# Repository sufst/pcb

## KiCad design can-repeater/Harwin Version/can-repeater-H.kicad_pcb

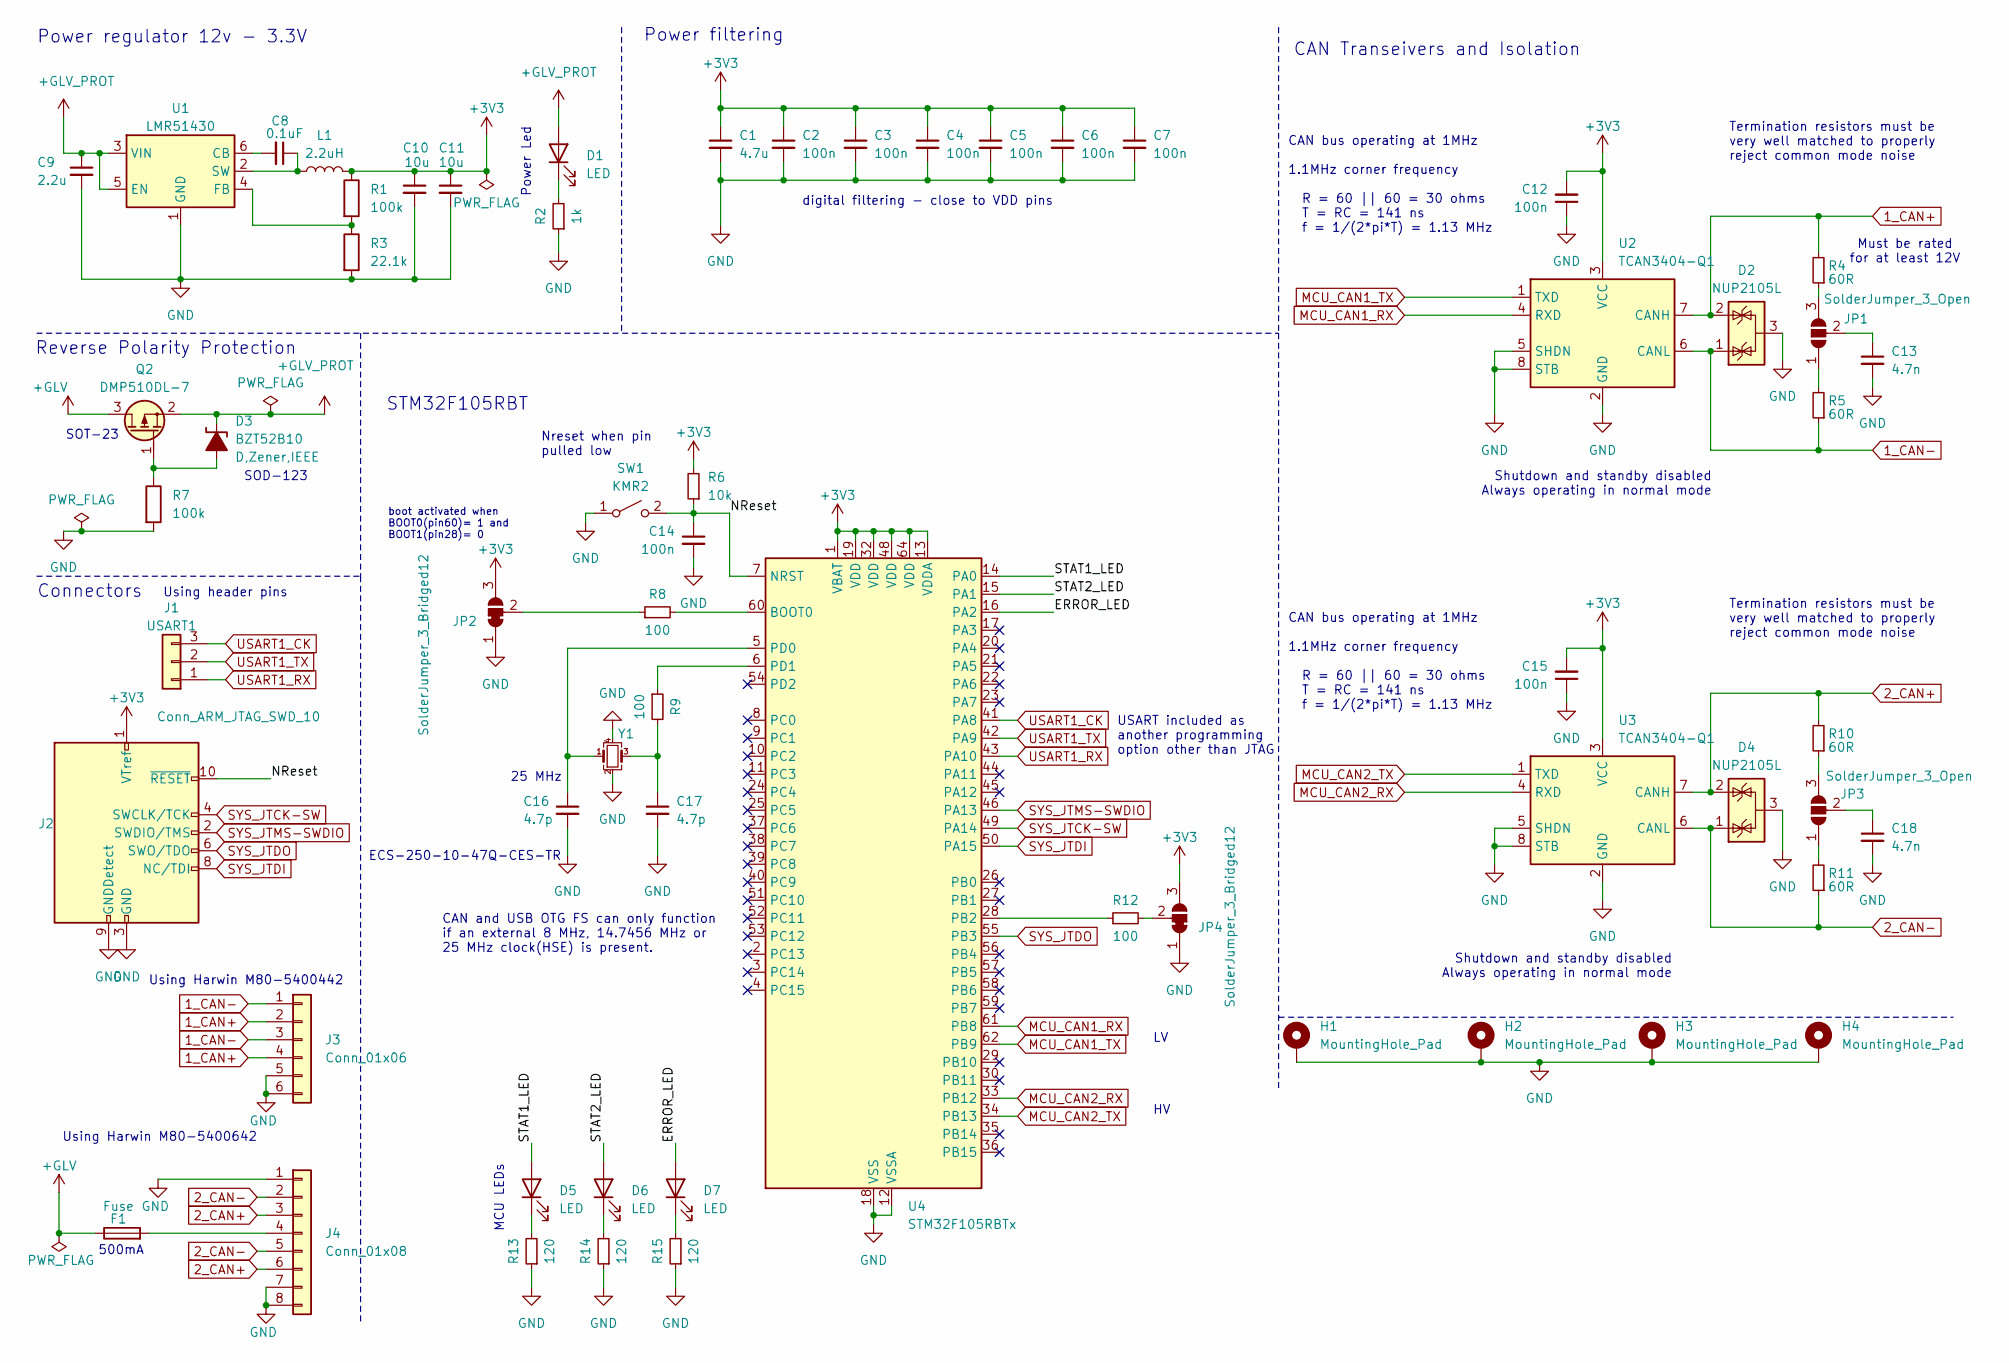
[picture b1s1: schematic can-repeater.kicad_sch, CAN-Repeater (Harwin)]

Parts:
C1: 4.7u; C_0805_2012Metric_Pad1.18x1.45mm_HandSolder
C2, C3, C4, C5, C6, C7, C12, C14, C15: 100n; C_0603_1608Metric_Pad1.08x0.95mm_HandSolder
C8: 0.1uF; C_0603_1608Metric_Pad1.08x0.95mm_HandSolder
C9: 2.2u; C_0603_1608Metric_Pad1.08x0.95mm_HandSolder
C10, C11: 10u; C_0805_2012Metric_Pad1.18x1.45mm_HandSolder
C13, C18: 4.7n; C_0603_1608Metric_Pad1.08x0.95mm_HandSolder
C16, C17: 4.7p; C_0603_1608Metric_Pad1.08x0.95mm_HandSolder
D1, D5, D6, D7: LED; LED_0805_2012Metric_Pad1.15x1.40mm_HandSolder
D2, D4: NUP2105L; SOT-23; MPN NUP2105L
D3: BZT52B10; D_SOD-123; MPN BZT52B10
F1: Fuse; Fuse_0603_1608Metric_Pad1.05x0.95mm_HandSolder
H1, H2, H3, H4: MountingHole_Pad; MountingHole_2.2mm_M2_DIN965_Pad_TopBottom
J1: USART1; PinHeader_1x03_P2.54mm_Vertical
J2: Conn_ARM_JTAG_SWD_10; SHF10501LDSMLC; MPN SHF-105-01-L-D-SM-LC
J3: Conn_01x06; M80-5400442; MPN M80-5400442
J4: Conn_01x08; M80-5400642; MPN M80-5400642
JP1, JP3: SolderJumper_3_Open; SolderJumper-3_P1.3mm_Open_RoundedPad1.0x1.5mm
JP2, JP4: SolderJumper_3_Bridged12; SolderJumper-3_P1.3mm_Bridged12_RoundedPad1.0x1.5mm
L1: 2.2uH; L_Coilcraft_XAL4020-XXX; MPN XAL4020-222MEC
Q2: DMP510DL-7; SOT-23
R1, R7: 100k; R_0603_1608Metric_Pad0.98x0.95mm_HandSolder
R2: 1k; R_0603_1608Metric_Pad0.98x0.95mm_HandSolder
R3: 22.1k; R_0603_1608Metric_Pad0.98x0.95mm_HandSolder
R4, R5, R10, R11: 60R; R_0603_1608Metric_Pad0.98x0.95mm_HandSolder
R6: 10k; R_0603_1608Metric_Pad0.98x0.95mm_HandSolder
R8, R9, R12: 100; R_0603_1608Metric_Pad0.98x0.95mm_HandSolder
R13, R14, R15: 120; R_0603_1608Metric_Pad0.98x0.95mm_HandSolder
SW1: KMR2; SW_Push_1P1T_NO_CK_KMR2; MPN KMR221NG LFS
U1: LMR51430; SOT-23-6; MPN LMR51430YDDCR
U2, U3: TCAN3404-Q1; SOT-23-8_Handsoldering; MPN TCAN3404DDFRQ1
U4: STM32F105RBTx; LQFP-64_10x10mm_P0.5mm; MPN STM32F105RBT6
Y1: ECS-250-10-47Q-CES-TR; Resonator_SMD_ECS_ECX-1247Q_1.6x1.2x0.3mm; MPN ECS-250-10-47Q-CES-TR

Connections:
1_CAN+: D2.2 (K), J3.2, J3.4, R4.2, U2.7 (CANH)
1_CAN-: D2.1 (K), J3.1, J3.3, R5.1, U2.6 (CANL)
2_CAN+: D4.2 (K), J4.3, J4.6, R10.2, U3.7 (CANH)
2_CAN-: D4.1 (K), J4.2, J4.5, R11.1, U3.6 (CANL)
+3V3: C1.1, C2.1, C3.1, C4.1, C5.1, C6.1, C7.1, C10.1, C11.1, C12.2, C15.2, J2.1 (VTref), JP2.3 (B), JP4.3 (B), L1.2, R1.1, R6.2, U2.3 (VCC), U3.3 (VCC), U4.1 (VBAT), U4.13 (VDDA), U4.19 (VDD), U4.32 (VDD), U4.48 (VDD), U4.64 (VDD)
+GLV: F1.1, Q2.3 (D)
+GLV_PROT: C9.1, D1.2 (A), D3.1 (K-), Q2.2 (S), U1.3 (VIN), U1.5 (EN)
/ERROR_LED: D7.2 (A), U4.16 (PA2)
/NReset: C14.1, J2.10 (~RESET), R6.1, SW1.2 (B), U4.7 (NRST)
/STAT1_LED: D5.2 (A), U4.14 (PA0)
/STAT2_LED: D6.2 (A), U4.15 (PA1)
GND: C1.2, C2.2, C3.2, C4.2, C5.2, C6.2, C7.2, C9.2, C10.2, C11.2, C12.1, C13.2, C14.2, C15.1, C16.2, C17.2, C18.2, D2.3 (A), D4.3 (A), H1.1, H2.1, H3.1, H4.1, J2.3 (GND), J2.5 (GND), J2.9 (GNDDetect), J3.5, J3.6, J4.1, J4.7, J4.8, JP2.1 (A), JP4.1 (A), R2.1, R3.2, R7.2, R13.1, R14.1, R15.1, SW1.1 (A), U1.1 (GND), U2.2 (GND), U2.5 (SHDN), U2.8 (STB), U3.2 (GND), U3.5 (SHDN), U3.8 (STB), U4.12 (VSSA), U4.18 (VSS), U4.31 (VSS), U4.47 (VSS), U4.63 (VSS), Y1.2, Y1.4
MCU_CAN1_RX: U2.4 (RXD), U4.61 (PB8)
MCU_CAN1_TX: U2.1 (TXD), U4.62 (PB9)
MCU_CAN2_RX: U3.4 (RXD), U4.33 (PB12)
MCU_CAN2_TX: U3.1 (TXD), U4.34 (PB13)
unnamed: C17.1, R9.2, Y1.3
unnamed: D1.1 (K), R2.2
unnamed: D3.2 (A+), Q2.1 (G), R7.1
unnamed: D5.1 (K), R13.2
unnamed: D6.1 (K), R14.2
unnamed: D7.1 (K), R15.2
unnamed: F1.2, J4.4
unnamed: JP1.1 (A), R5.2
unnamed: JP1.3 (B), R4.1
unnamed: C13.1, JP1.2 (C)
unnamed: JP2.2 (C), R8.1
unnamed: JP3.1 (A), R11.2
unnamed: JP3.3 (B), R10.1
unnamed: C18.1, JP3.2 (C)
unnamed: JP4.2 (C), R12.2
unnamed: C8.2, U1.6 (CB)
unnamed: R1.2, R3.1, U1.4 (FB)
unnamed: C8.1, L1.1, U1.2 (SW)
unnamed: R8.2, U4.60 (BOOT0)
unnamed: R12.1, U4.28 (PB2)
unnamed: C16.1, U4.5 (PD0), Y1.1
unnamed: R9.1, U4.6 (PD1)
SYS_JTCK-SW: J2.4 (SWCLK/TCK), U4.49 (PA14)
SYS_JTDI: J2.8 (NC/TDI), U4.50 (PA15)
SYS_JTDO: J2.6 (SWO/TDO), U4.55 (PB3)
SYS_JTMS-SWDIO: J2.2 (SWDIO/TMS), U4.46 (PA13)
USART1_CK: J1.3, U4.41 (PA8)
USART1_RX: J1.1, U4.43 (PA10)
USART1_TX: J1.2, U4.42 (PA9)

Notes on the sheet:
Using header pins
Shutdown and standby disabled Always operating in normal mode
MCU LEDs
SOT-23
ECS-250-10-47Q-CES-TR
Termination resistors must be very well matched to properly reject common mode noise
boot activated when BOOT0(pin60)= 1 and BOOT1(pin28)= 0
CAN and USB OTG FS can only function if an external 8 MHz, 14.7456 MHz or 25 MHz clock(HSE) is present.
Using Harwin M80-5400442
Power Led
Power regulator 12v - 3.3V
Nreset when pin pulled low
Reverse Polarity Protection
digital filtering - close to VDD pins
CAN bus operating at 1MHz 1.1MHz corner frequency R = 60 || 60 = 30 ohms T = RC = 141 ns f = 1/(2*pi*T) = 1.13 MHz
SOD-123
CAN Transeivers and Isolation
500mA
Connectors
STM32F105RBT
25 MHz
Using Harwin M80-5400642
Must be rated for at least 12V
USART included as another programming option other than JTAG
Power filtering

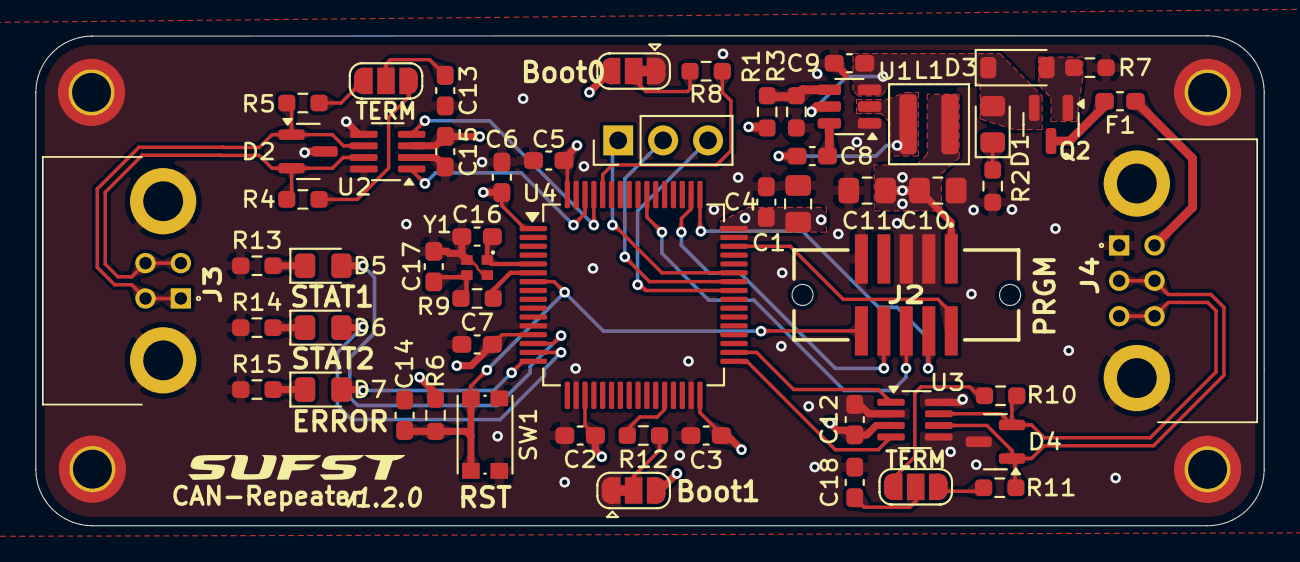
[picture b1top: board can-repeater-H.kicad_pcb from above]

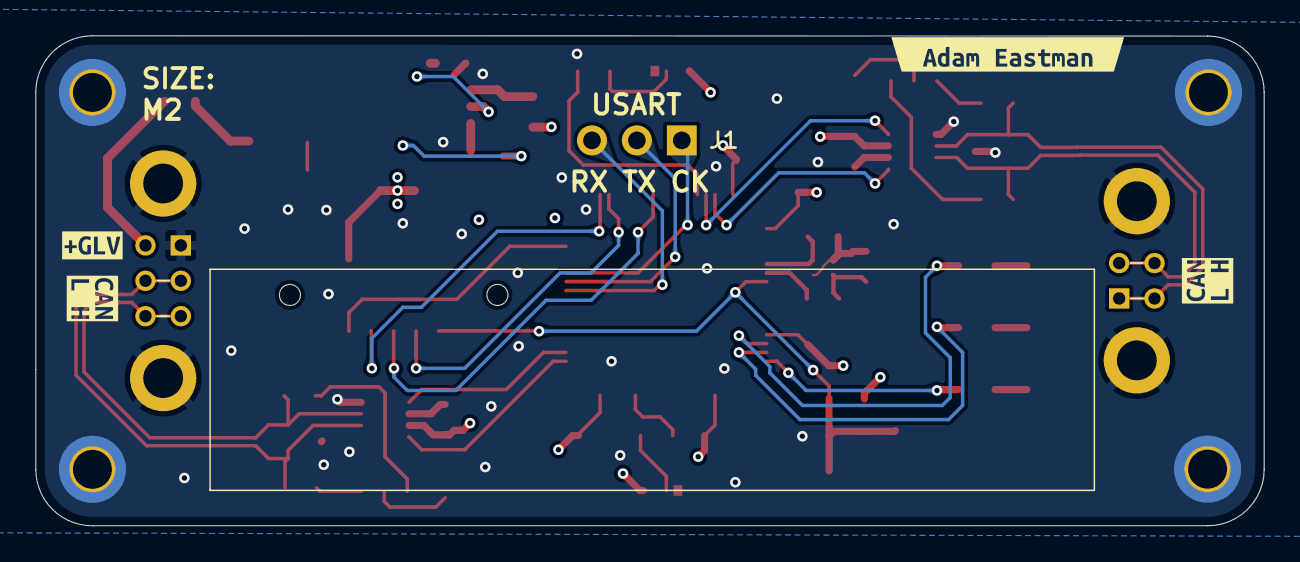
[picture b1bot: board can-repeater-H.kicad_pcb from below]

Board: 4 copper layers, 69.5 x 27.7 mm, 65 parts (4 on the bottom side), 45 nets.

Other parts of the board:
kibuzzard-694AF8B0: G***; kibuzzard-694AF8B0
kibuzzard-694AF877: G***; kibuzzard-694AF877
kibuzzard-6972BB08: G***; kibuzzard-6972BB08
kibuzzard-6972C6E9: G***; kibuzzard-6972C6E9

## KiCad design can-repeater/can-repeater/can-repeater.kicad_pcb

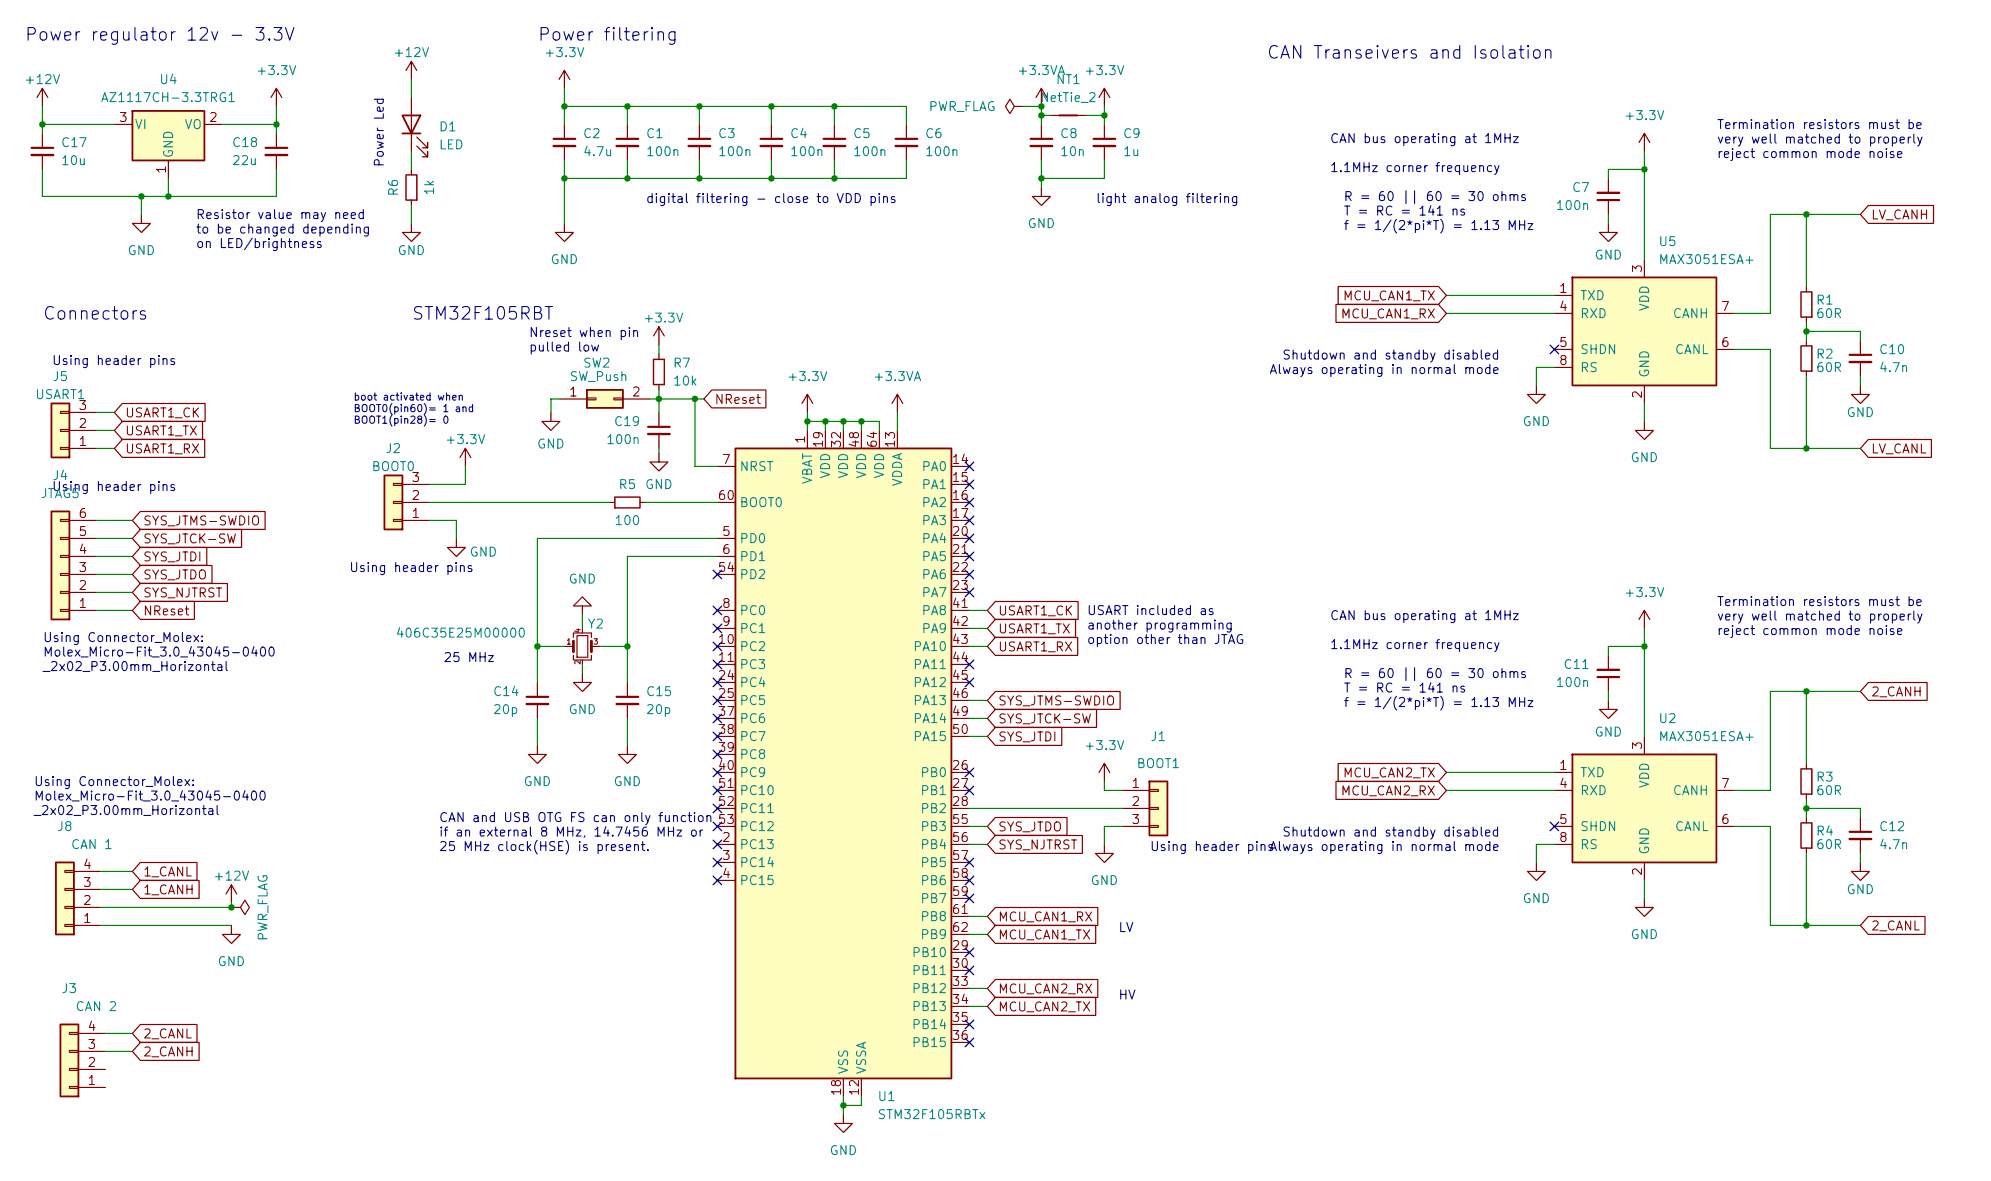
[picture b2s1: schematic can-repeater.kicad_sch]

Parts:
C1, C3, C4, C5, C6, C7, C11, C19: 100n; C_0805_2012Metric_Pad1.18x1.45mm_HandSolder
C2: 4.7u; C_1206_3216Metric_Pad1.33x1.80mm_HandSolder
C8: 10n; C_0805_2012Metric_Pad1.18x1.45mm_HandSolder
C9: 1u; C_0805_2012Metric_Pad1.18x1.45mm_HandSolder
C10, C12: 4.7n; C_0805_2012Metric_Pad1.18x1.45mm_HandSolder
C14, C15: 20p; C_0805_2012Metric_Pad1.18x1.45mm_HandSolder
C17: 10u; C_1206_3216Metric_Pad1.33x1.80mm_HandSolder
C18: 22u; C_1206_3216Metric_Pad1.33x1.80mm_HandSolder
D1: LED; LED_0805_2012Metric_Pad1.15x1.40mm_HandSolder
J1: BOOT1; PinHeader_1x03_P2.54mm_Vertical
J2: BOOT0; PinHeader_1x03_P2.54mm_Vertical
J3: CAN 2; Molex_Micro-Fit_3.0_43045-0400_2x02_P3.00mm_Horizontal
J4: JTAG5; PinHeader_1x06_P2.54mm_Vertical
J5: USART1; PinHeader_1x03_P2.54mm_Vertical
J8: CAN 1; Molex_Micro-Fit_3.0_43045-0400_2x02_P3.00mm_Horizontal
NT1: NetTie_2; NetTie-2_SMD_Pad0.5mm
R1, R2, R3, R4: 60R; R_0805_2012Metric_Pad1.20x1.40mm_HandSolder
R5: 100; R_0805_2012Metric_Pad1.20x1.40mm_HandSolder
R6: 1k; R_0805_2012Metric_Pad1.20x1.40mm_HandSolder
R7: 10k; R_0805_2012Metric_Pad1.20x1.40mm_HandSolder
SW2: SW_Push; PinHeader_1x02_P2.54mm_Vertical
U1: STM32F105RBTx; LQFP-64_10x10mm_P0.5mm
U2, U5: MAX3051ESA+; SOIC-8_3.9x4.9mm_P1.27mm
U4: AZ1117CH-3.3TRG1; SOT-223-3_TabPin2
Y2: 406C35E25M00000; Crystal_SMD_0603-4Pin_6.0x3.5mm_HandSoldering

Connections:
1_CANH: J8.3
1_CANL: J8.4
2_CANH: J3.3, R3.2, U2.7 (CANH)
2_CANL: J3.4, R4.1, U2.6 (CANL)
+3.3V: C1.1, C2.1, C3.1, C4.1, C5.1, C6.1, C7.2, C9.1, C11.2, C18.1, J1.1, J2.3, NT1.2, R7.2, U1.1 (VBAT), U1.19 (VDD), U1.32 (VDD), U1.48 (VDD), U1.64 (VDD), U2.3 (VDD), U4.2 (VO), U5.3 (VDD)
+3.3VA: C8.1, NT1.1, U1.13 (VDDA)
+12V: C17.1, D1.2 (A), J8.2, U4.3 (VI)
GND: C1.2, C2.2, C3.2, C4.2, C5.2, C6.2, C7.1, C8.2, C9.2, C10.2, C11.1, C12.2, C14.2, C15.2, C17.2, C18.2, C19.2, J1.3, J2.1, J8.1, R6.1, SW2.1, U1.12 (VSSA), U1.18 (VSS), U1.31 (VSS), U1.47 (VSS), U1.63 (VSS), U2.2 (GND), U2.8 (RS), U4.1 (GND), U5.2 (GND), U5.8 (RS), Y2.2, Y2.4
LV_CANH: R1.2, U5.7 (CANH)
LV_CANL: R2.1, U5.6 (CANL)
MCU_CAN1_RX: U1.61 (PB8), U5.4 (RXD)
MCU_CAN1_TX: U1.62 (PB9), U5.1 (TXD)
MCU_CAN2_RX: U1.33 (PB12), U2.4 (RXD)
MCU_CAN2_TX: U1.34 (PB13), U2.1 (TXD)
NReset: C19.1, J4.1, R7.1, SW2.2, U1.7 (NRST)
unnamed: C10.1, R1.1, R2.2
unnamed: C12.1, R3.1, R4.2
unnamed: D1.1 (K), R6.2
unnamed: J1.2, U1.28 (PB2)
unnamed: J2.2, R5.1
unnamed: R5.2, U1.60 (BOOT0)
unnamed: C14.1, U1.5 (PD0), Y2.1
unnamed: C15.1, U1.6 (PD1), Y2.3
SYS_JTCK-SW: J4.5, U1.49 (PA14)
SYS_JTDI: J4.4, U1.50 (PA15)
SYS_JTDO: J4.3, U1.55 (PB3)
SYS_JTMS-SWDIO: J4.6, U1.46 (PA13)
SYS_NJTRST: J4.2, U1.56 (PB4)
USART1_CK: J5.3, U1.41 (PA8)
USART1_RX: J5.1, U1.43 (PA10)
USART1_TX: J5.2, U1.42 (PA9)

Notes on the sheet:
Using header pins
Shutdown and standby disabled Always operating in normal mode
Termination resistors must be very well matched to properly reject common mode noise
boot activated when BOOT0(pin60)= 1 and BOOT1(pin28)= 0
CAN and USB OTG FS can only function if an external 8 MHz, 14.7456 MHz or 25 MHz clock(HSE) is present.
Using Connector_Molex: Molex_Micro-Fit_3.0_43045-0400 _2x02_P3.00mm_Horizontal
Power Led
Power regulator 12v - 3.3V
Nreset when pin pulled low
digital filtering - close to VDD pins
CAN bus operating at 1MHz 1.1MHz corner frequency R = 60 || 60 = 30 ohms T = RC = 141 ns f = 1/(2*pi*T) = 1.13 MHz
CAN Transeivers and Isolation
Resistor value may need to be changed depending on LED/brightness
light analog filtering
Connectors
STM32F105RBT
25 MHz
USART included as another programming option other than JTAG
Power filtering

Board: 2 copper layers, 37 parts (0 on the bottom side), 29 nets, no tracks yet.

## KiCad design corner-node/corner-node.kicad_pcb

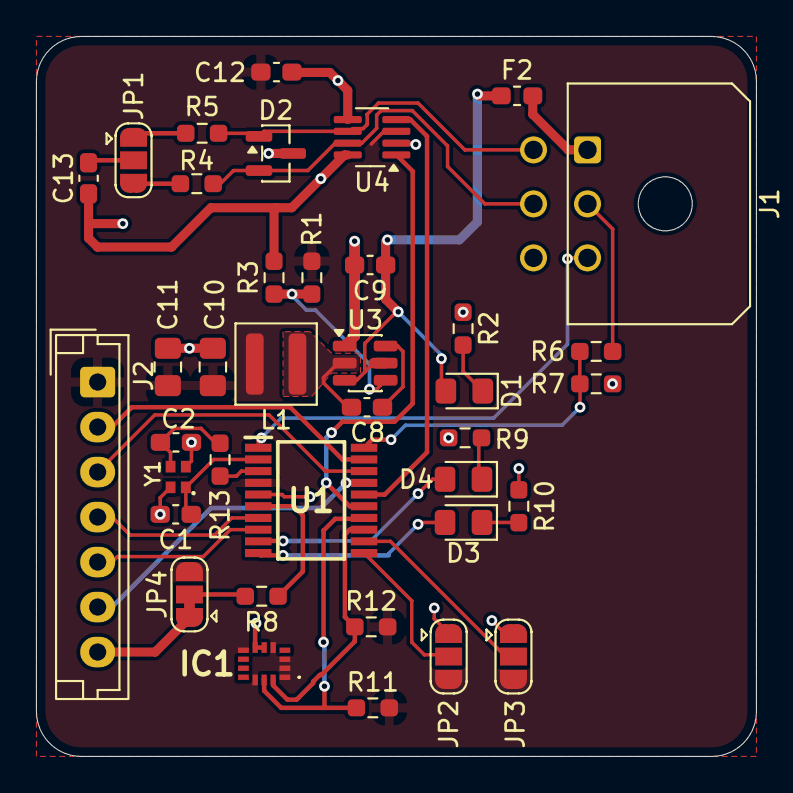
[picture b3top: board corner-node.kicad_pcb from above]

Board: 2 copper layers, 40.0 x 40.0 mm, 38 parts (0 on the bottom side), 36 nets.

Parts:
C1, C2: C; C_0603_1608Metric_Pad1.08x0.95mm_HandSolder
C8: 0.1uF; C_0603_1608Metric_Pad1.08x0.95mm_HandSolder
C9: 2.2u; C_0603_1608Metric_Pad1.08x0.95mm_HandSolder
C10, C11: 10u; C_0805_2012Metric_Pad1.18x1.45mm_HandSolder
C12: 100n; C_0603_1608Metric_Pad1.08x0.95mm_HandSolder
C13: 4.7n; C_0603_1608Metric_Pad1.08x0.95mm_HandSolder
D1, D3, D4: LED; LED_0805_2012Metric_Pad1.15x1.40mm_HandSolder
D2: NUP2105L; SOT-23
F2: Fuse; Fuse_0603_1608Metric_Pad1.05x0.95mm_HandSolder
IC1: LSM6DSV80XTR; LSM6DSV16BXTR
J1: Conn_01x06; Molex_Micro-Fit_3.0_43045-0600_2x03_P3.00mm_Horizontal
J2: Conn_01x07; JST_EH_B7B-EH-A_1x07_P2.50mm_Vertical
JP1, JP2, JP3: SolderJumper_3_Open; SolderJumper-3_P1.3mm_Open_RoundedPad1.0x1.5mm
JP4: SolderJumper_3_Bridged12; SolderJumper-3_P1.3mm_Bridged12_RoundedPad1.0x1.5mm
L1: 2.2uH; L_Coilcraft_XAL4020-XXX
R1: 100k; R_0603_1608Metric_Pad0.98x0.95mm_HandSolder
R2: 1k; R_0603_1608Metric_Pad0.98x0.95mm_HandSolder
R3: 22.1k; R_0603_1608Metric_Pad0.98x0.95mm_HandSolder
R4, R5: 60R; R_0603_1608Metric_Pad0.98x0.95mm_HandSolder
R6: 30k; R_0603_1608Metric_Pad0.98x0.95mm_HandSolder
R7: 10k; R_0603_1608Metric_Pad0.98x0.95mm_HandSolder
R8, R13: 100; R_0603_1608Metric_Pad0.98x0.95mm_HandSolder
R9, R10: 120; R_0603_1608Metric_Pad0.98x0.95mm_HandSolder
R11, R12: 4.7k; R_0603_1608Metric_Pad0.98x0.95mm_HandSolder
U1: SOP65P640X120-20N
U3: LMR51430; SOT-23-6
U4: TCAN3404-Q1; SOT-23-8_Handsoldering
Y1: ECS-250-10-47Q-CES-TR; Resonator_SMD_ECS_ECX-1247Q_1.6x1.2x0.3mm

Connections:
1_CAN+: D2.2 (K), J1.5, R4.2, U4.7 (CANH)
1_CAN-: D2.1 (K), J1.4, R5.1, U4.6 (CANL)
+3V3: C10.1, C11.1, C12.2, IC1.1 (SDO/SA0), IC1.2 (SDX), IC1.3 (SCX), IC1.5 (VDDIO), IC1.8 (VDD), IC1.12 (CS), J2.1, JP2.3 (B), JP3.3 (B), JP4.3 (B), L1.2, R1.1, R11.2, R12.2, U1.4 (VDD), U4.3 (VCC)
+GLV_PROT: C9.1, D1.2 (A), F2.1, U3.3 (VIN), U3.5 (EN)
/BOOT0: R8.1, U1.6 (PF2)
/DEBUG_SWCLK: J2.2, U1.19 (PA14)
/DEBUG_SWDIO: J2.3, U1.18 (PA13)
/ERROR_LED: D3.2 (A), U1.10 (PA3)
/FDCAN1_RX: U1.16 (PA11), U4.4 (RXD)
/FDCAN1_TX: U1.15 (PB0), U4.1 (TXD)
/I2C2_SCL: IC1.13 (SCL), R11.1, U1.14 (PA7)
/I2C2_SDA: IC1.14 (SDA), R12.1, U1.13 (PA6)
/PPS_IN: J1.3, U1.1 (PB7)
/RCC_OSCX_IN: C1.1, U1.2 (PC14), Y1.1
/RCC_OSCX_OUT: R13.1, U1.3 (PC15)
/STATUS1_LED: D4.2 (A), U1.9 (PA2)
/USART1_CK: J2.6, U1.17 (PA12)
/USART1_RX: J2.5, U1.8 (PA1)
/USART1_TX: J2.4, U1.7 (PA0)
/WHEELSPEED IN: R6.2, R7.1, U1.20 (PB3)
/WHEELSPEED sensor: J1.2, R6.1
/WHEEL_ID0: JP2.2 (C), U1.11 (PA4)
/WHEEL_ID1: JP3.2 (C), U1.12 (PA5)
GND: C1.2, C2.2, C9.2, C10.2, C11.2, C12.1, C13.2, D2.3 (A), IC1.6 (GND_1), IC1.7 (GND_2), J1.6, J2.7, JP2.1 (A), JP3.1 (A), JP4.1 (A), R2.1, R3.2, R7.2, R9.1, R10.1, U1.5 (VSS), U3.1 (GND), U4.2 (GND), U4.5 (SHDN), U4.8 (STB), Y1.2, Y1.4
unnamed: C2.1, R13.2, Y1.3
unnamed: D1.1 (K), R2.2
unnamed: D3.1 (K), R10.2
unnamed: D4.1 (K), R9.2
unnamed: F2.2, J1.1
unnamed: JP1.1 (A), R5.2
unnamed: JP1.3 (B), R4.1
unnamed: C13.1, JP1.2 (C)
unnamed: JP4.2 (C), R8.2
unnamed: C8.2, U3.6 (CB)
unnamed: R1.2, R3.1, U3.4 (FB)
unnamed: C8.1, L1.1, U3.2 (SW)

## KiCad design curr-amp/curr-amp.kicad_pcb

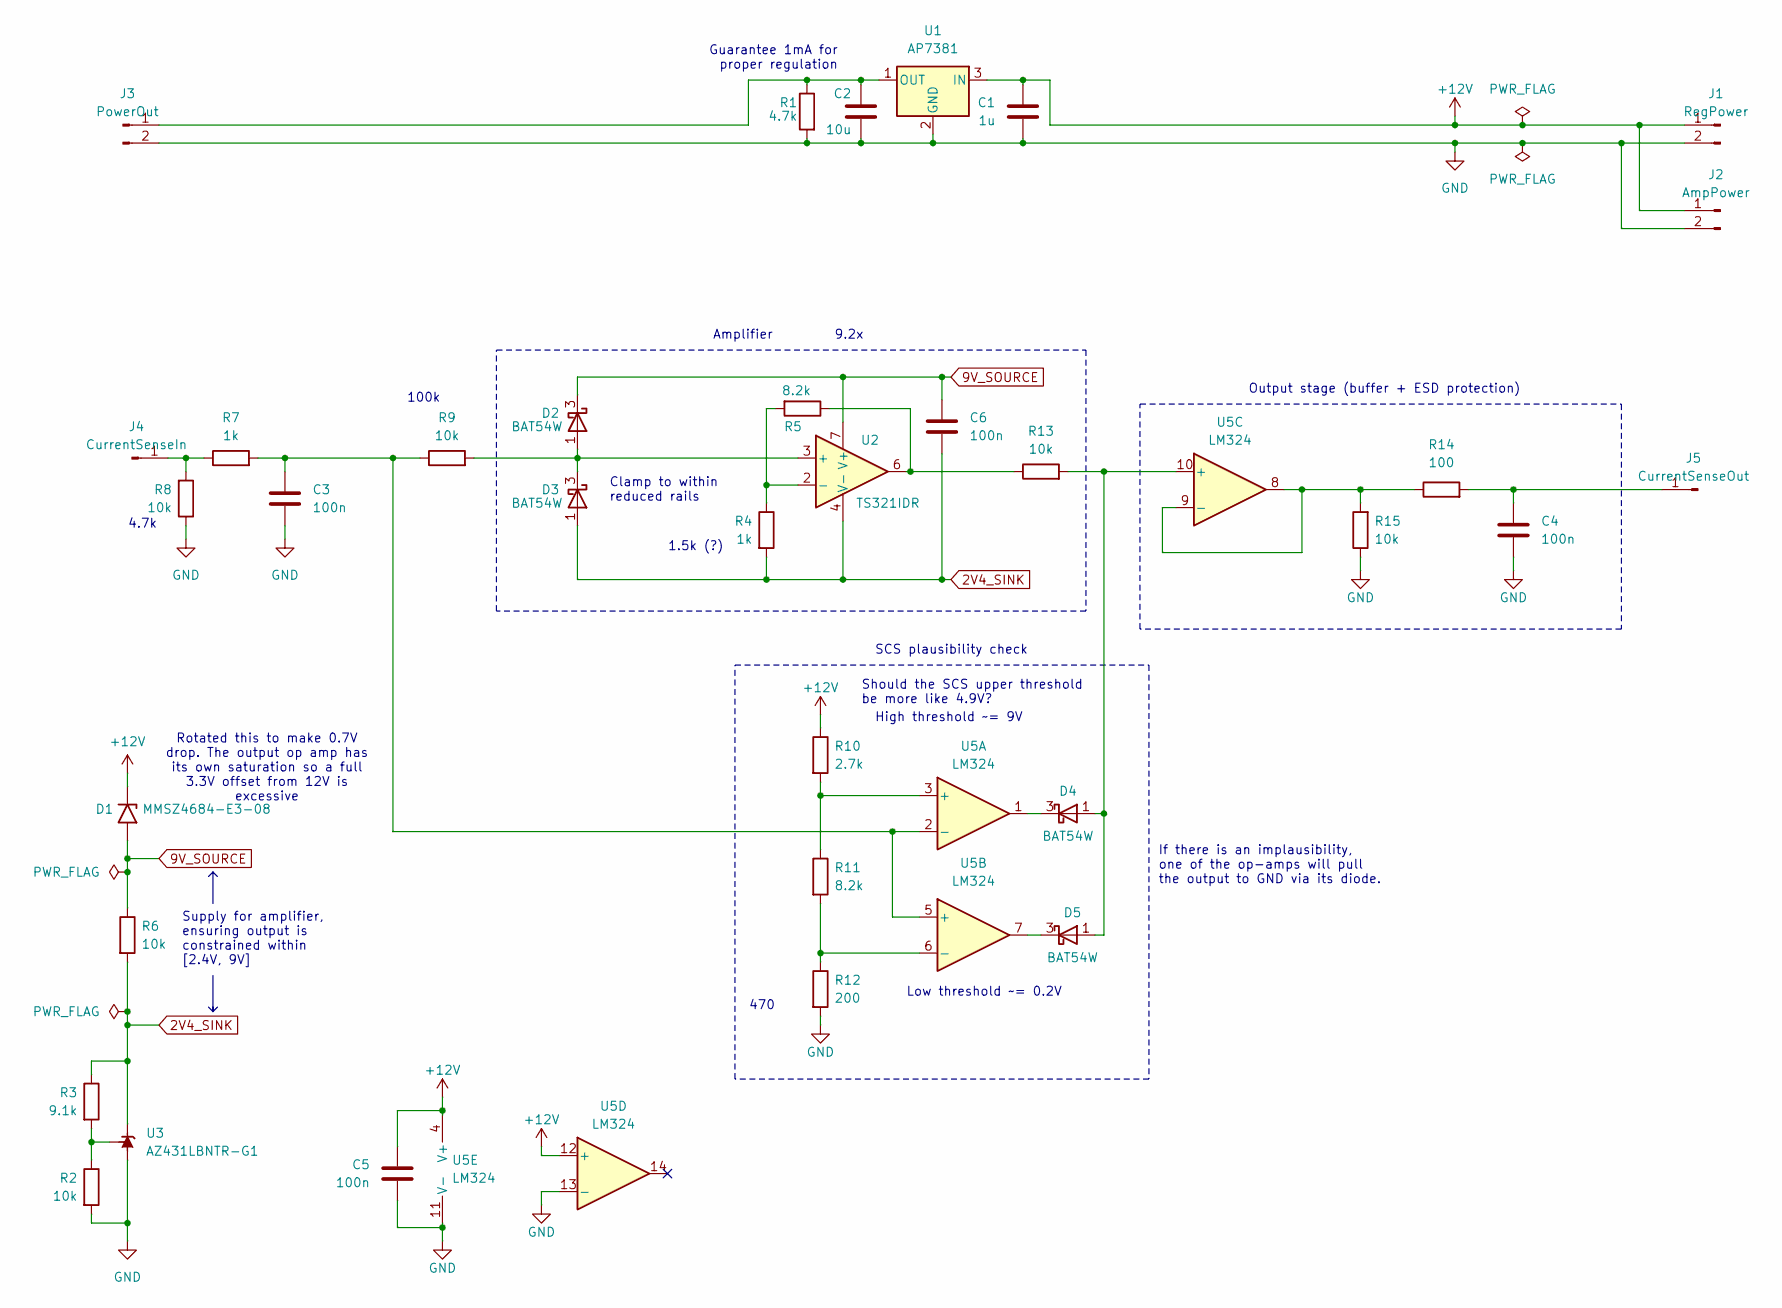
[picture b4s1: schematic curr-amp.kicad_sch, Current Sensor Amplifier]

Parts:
C1: 1u; C_0805_2012Metric_Pad1.18x1.45mm_HandSolder
C2: 10u; C_0805_2012Metric_Pad1.18x1.45mm_HandSolder
C3, C4, C5, C6: 100n; C_0805_2012Metric_Pad1.18x1.45mm_HandSolder
D1: MMSZ4684-E3-08; D_SOD-123
D2, D3, D4, D5: BAT54W; SOT-323_SC-70
J1: RegPower; PinHeader_1x02_P2.54mm_Vertical
J2: AmpPower; PinHeader_1x02_P2.54mm_Vertical
J3: PowerOut; PinHeader_1x02_P2.54mm_Vertical
J4: CurrentSenseIn; PinHeader_1x01_P2.54mm_Vertical
J5: CurrentSenseOut; PinHeader_1x01_P2.54mm_Vertical
R1: 4.7k; R_0805_2012Metric_Pad1.20x1.40mm_HandSolder
R2, R6, R8, R9, R13, R15: 10k; R_0805_2012Metric_Pad1.20x1.40mm_HandSolder
R3: 9.1k; R_0805_2012Metric_Pad1.20x1.40mm_HandSolder
R4, R7: 1k; R_0805_2012Metric_Pad1.20x1.40mm_HandSolder
R5, R11: 8.2k; R_0805_2012Metric_Pad1.20x1.40mm_HandSolder
R10: 2.7k; R_0805_2012Metric_Pad1.20x1.40mm_HandSolder
R12: 200; R_0805_2012Metric_Pad1.20x1.40mm_HandSolder
R14: 100; R_0805_2012Metric_Pad1.20x1.40mm_HandSolder
U1: AP7381; SOT-89-3
U2: TS321IDR; SOIC-8_3.9x4.9mm_P1.27mm
U3: AZ431LBNTR-G1; SOT-23_Handsoldering
U5: LM324; SOIC-14_3.9x8.7mm_P1.27mm

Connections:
2V4_SINK: C6.2, D3.1 (A), R3.1, R4.2, R6.2, U2.4 (V-), U3.2 (K)
9V_SOURCE: C6.1, D1.2 (A2), D2.3 (K), R6.1, U2.7 (V+)
+12V: C1.1, C5.1, D1.1 (A1), J1.1, J2.1, R10.1, U1.3 (IN), U5.4 (V+), U5.12 (+)
GND: C1.2, C2.2, C3.2, C4.2, C5.2, J1.2, J2.2, J3.2, R1.2, R2.2, R8.1, R12.2, R15.1, U1.2 (GND), U3.3 (A), U5.11 (V-), U5.13 (-)
unnamed: D2.1 (A), D3.3 (K), R9.2, U2.3 (+)
unnamed: D4.1 (A), D5.1 (A), R13.2, U5.10 (+)
unnamed: D4.3 (K), U5.1
unnamed: D5.3 (K), U5.7
unnamed: C2.1, J3.1, R1.1, U1.1 (OUT)
unnamed: J4.1, R7.1, R8.2
unnamed: C4.1, J5.1, R14.2
unnamed: R5.1, R13.1, U2.6
unnamed: R4.1, R5.2, U2.2 (-)
unnamed: R2.1, R3.2, U3.1 (REF)
unnamed: R10.2, R11.1, U5.3 (+)
unnamed: C3.1, R7.2, R9.1, U5.2 (-), U5.5 (+)
unnamed: R11.2, R12.1, U5.6 (-)
unnamed: R14.1, R15.2, U5.8, U5.9 (-)

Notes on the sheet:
1.5k (?)
9.2x
Rotated this to make 0.7V drop. The output op amp has its own saturation so a full 3.3V offset from 12V is excessive
Low threshold ~= 0.2V
Output stage (buffer + ESD protection)
Clamp to within reduced rails
Guarantee 1mA for proper regulation
If there is an implausibility, one of the op-amps will pull the output to GND via its diode.
Amplifier
470
100k
4.7k
SCS plausibility check
High threshold ~= 9V
Should the SCS upper threshold be more like 4.9V?
Supply for amplifier, ensuring output is constrained within [2.4V, 9V]

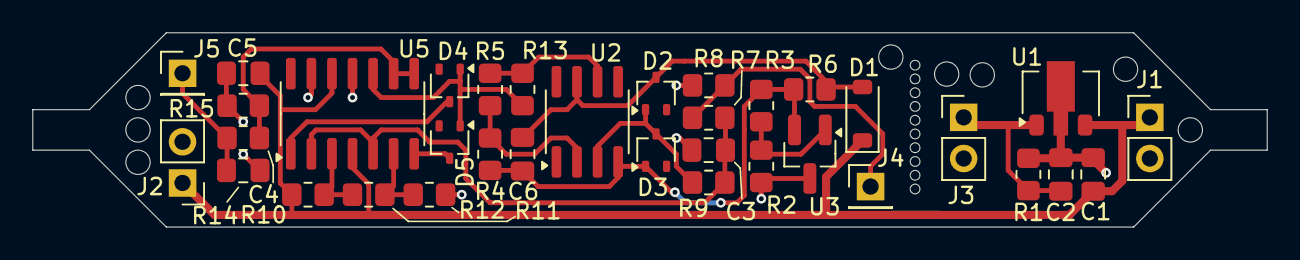
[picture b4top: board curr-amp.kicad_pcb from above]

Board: 2 copper layers, 76.2 x 12.0 mm, 35 parts (0 on the bottom side), 18 nets.

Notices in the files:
parts and their libraries:
License: Apache-2.0
